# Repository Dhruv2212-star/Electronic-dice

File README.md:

# Electronic Dice
Tired of Board game tactics and cheating???? 
**I present an ELECTRONIC dice**  
A small 30mm x  30mm module which has 6 LEDs. when u press a button it changes LEDs quickly and random leds turn on from 1-6.  

# How to use?? 
It's simple enough for a todler to use ! just press a button and you get a random no. of LEDs!  
**Final assembly image**  

*You know what else is cool??*
the PCB, it uses minimal components at surface to keep it super clean!  

# Firmware Flashing
connect your debugger probe to the J2 port accordingly for this first.  
Our Pinc connections on PCB  

| J2 pin | Signal | ATtiny84A |  
| -----: | ------ | --------- |  
|      1 | VCC    | U1 pin 1  |  
|      2 | GND    | U1 pin 14 |    
|      3 | MOSI   | PB0       |  
|      4 | MISO   | PB1       |    
|      5 | SCK    | PB2       |    
|      6 | RESET  | PB3       |  

**Install Arduino IDE**  
then,  
File-> prefrences  
-additional board manager URLs  
--https://drazzy.com/package_drazzy.com_index.json  
Tools->Boards->Board manager  
install "ATTinyCore"  

Select our board by: Tools-> Board-> ATTinny84a  
then set:  
| Arduino setting | Value              |  
| --------------- | ------------------ |  
| Chip            | **ATtiny84A**      |  
| Clock           | **1 MHz internal** |  
| B.O.D.          | **Disabled**       |  
| EEPROM          | **Retained**       |  
| Programmer      | **USBasp**         |  

**Connect USBasp**  
(power the pcb off first)  
connect: USBasp -> J2  
**Burn the config**  
**Upload dice firmware**  

# That's it !!

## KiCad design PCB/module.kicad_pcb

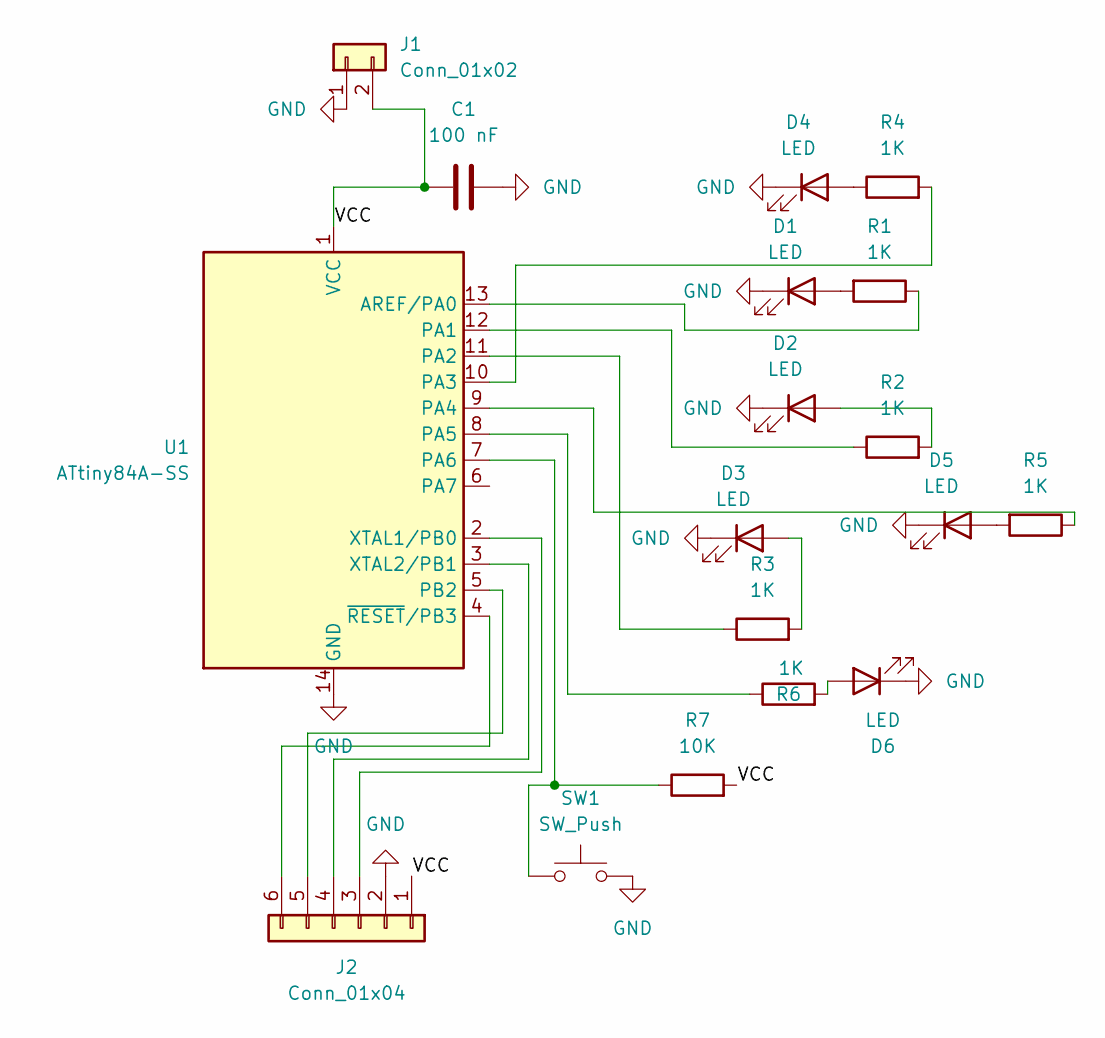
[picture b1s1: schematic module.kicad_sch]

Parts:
C1: 100 nF; C_1206_3216Metric
D1, D2, D3, D4, D5, D6: LED; LED_1206_3216Metric_Pad1.42x1.75mm_HandSolder
J1: Conn_01x02; PinHeader_1x02_P2.54mm_Vertical
J2: Conn_01x04; PinHeader_1x06_P2.54mm_Vertical
R1, R2, R3, R4, R5, R6: 1K; R_1206_3216Metric
R7: 10K; R_1206_3216Metric
SW1: SW_Push; SW_PUSH_6mm_H5mm
U1: ATtiny84A-SS; SOIC-14_3.9x8.7mm_P1.27mm

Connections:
/VCC: C1.1, J1.2, J2.1, R7.2, U1.1 (VCC)
GND: C1.2, D1.1 (K), D2.1 (K), D3.1 (K), D4.1 (K), D5.1 (K), D6.1 (K), J1.1, J2.2, SW1.2, U1.14 (GND)
unnamed: D1.2 (A), R1.2
unnamed: D2.2 (A), R2.2
unnamed: D3.2 (A), R3.2
unnamed: D4.2 (A), R4.1
unnamed: D5.2 (A), R5.2
unnamed: D6.2 (A), R6.2
unnamed: J2.3, U1.2 (XTAL1/PB0)
unnamed: J2.4, U1.3 (XTAL2/PB1)
unnamed: J2.5, U1.5 (PB2)
unnamed: J2.6, U1.4 (~RESET/PB3)
unnamed: R1.1, U1.13 (AREF/PA0)
unnamed: R2.1, U1.12 (PA1)
unnamed: R3.1, U1.11 (PA2)
unnamed: R4.2, U1.10 (PA3)
unnamed: R5.1, U1.9 (PA4)
unnamed: R6.1, U1.8 (PA5)
unnamed: R7.1, SW1.1, U1.7 (PA6)

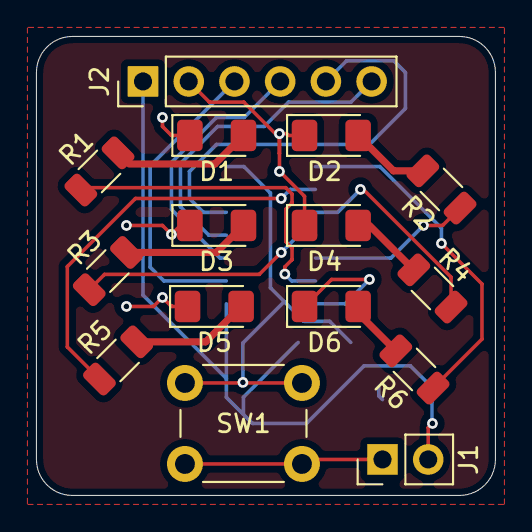
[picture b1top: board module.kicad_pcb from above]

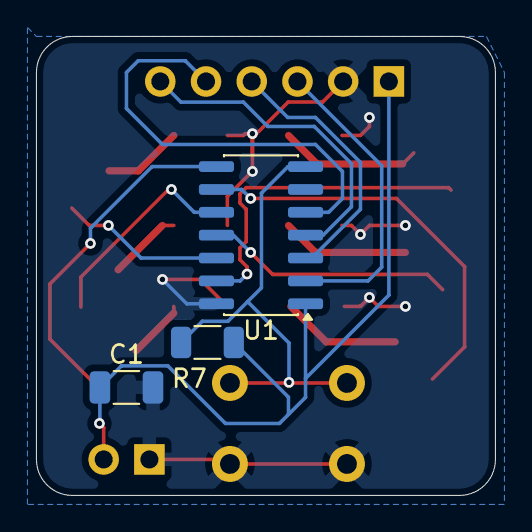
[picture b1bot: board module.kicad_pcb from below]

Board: 2 copper layers, 25.5 x 25.5 mm, 18 parts (3 on the bottom side), 19 nets.

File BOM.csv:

ref,value,quantity,symbol,footprint,unit_price_inr,supplier,buy_link,extended_price_inr
U1,ATtiny84A-SSU,1,MCU_Microchip_ATtiny:ATtiny84A-SS,Package_SO:SOIC-14_3.9x8.7mm_P1.27mm,80.54,Evelta,https://evelta.com/attiny84a-ssu-ic-mcu-8bit-8kb-flash-14soic/,80.54
D1-D6,White LED 1206,6,Device:LED,LED_SMD:LED_1206_3216Metric_Pad1.42x1.75mm_HandSolder,0.8,KTRON India,https://www.ktron.in/product/smd-white-led-1206-package/,4.800000000000001
R1-R6,1kΩ,6,Device:R,Resistor_SMD:R_1206_3216Metric,3.0,Probots,https://probots.co.in/1k-smd-resistor.html,18.0
R7,10kΩ,1,Device:R,Resistor_SMD:R_1206_3216Metric,3.0,Probots,https://probots.co.in/10k-smd-resistor.html,3.0
C1,100nF 50V,1,Device:C,Capacitor_SMD:C_1206_3216Metric,1.82,KTRON India,https://www.ktron.in/product/100nf-50v-104-mlcc-1206/,1.82
SW1,6x6x5mm tactile push button,1,Switch:SW_Push,Button_Switch_THT:SW_PUSH_6mm_H5mm,1.0,Techtonics,https://techtonics.in/product/tactile-push-button-switch-4-p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,1.0
J1,1x2 2.54mm male header,1,Connector_Generic:Conn_01x02,Connector_PinHeader_2.54mm:PinHeader_1x02_P2.54mm_Vertical,1.37,Sharvi Electronics,https://sharvielectronics.com/product-category/component/com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,1.37
J2,1x6 2.54mm male header,1,Connector_Generic:Conn_01x06,Connector_PinHeader_2.54mm:PinHeader_1x06_P2.54mm_Vertical,2.3,Sharvi Electronics,https://sharvielectronics.com/product-category/component/com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,2.3
TOTAL,,,,,,,,112.83

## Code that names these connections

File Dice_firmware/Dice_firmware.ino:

const uint8_t ledPins[6] = {
  PA0, PA1, PA2, PA3, PA4, PA5
};

const uint8_t buttonPin = PA6;

void showCount(uint8_t count) {
 
  for (uint8_t i = 0; i < 6; i++) {
    digitalWrite(ledPins[i], LOW);
  }

  
  uint8_t order[6] = {0, 1, 2, 3, 4, 5};

  for (int8_t i = 5; i > 0; i--) {
    uint8_t j = random(i + 1);

    uint8_t temp = order[i];
    order[i] = order[j];
    order[j] = temp;
  }

  for (uint8_t i = 0; i < count; i++) {
    digitalWrite(ledPins[order[i]], HIGH);
  }
}

void setup() {
  for (uint8_t i = 0; i < 6; i++) {
    pinMode(ledPins[i], OUTPUT);
    digitalWrite(ledPins[i], LOW);
  }

  pinMode(buttonPin, INPUT_PULLUP);

 
  randomSeed(analogRead(A7));
}

void loop() {
 
  if (digitalRead(buttonPin) == LOW) {

   
    delay(25);

    if (digitalRead(buttonPin) == LOW) {

      
      unsigned long startTime = millis();

      while (millis() - startTime < 2000UL) {
        uint8_t rollingCount = random(1, 7);
        showCount(rollingCount);

        delay(80);
      }

      
      uint8_t result = random(1, 7);
      showCount(result);

      
      while (digitalRead(buttonPin) == LOW) {
        delay(5);
      }

      
      delay(30);
    }
  }
}
